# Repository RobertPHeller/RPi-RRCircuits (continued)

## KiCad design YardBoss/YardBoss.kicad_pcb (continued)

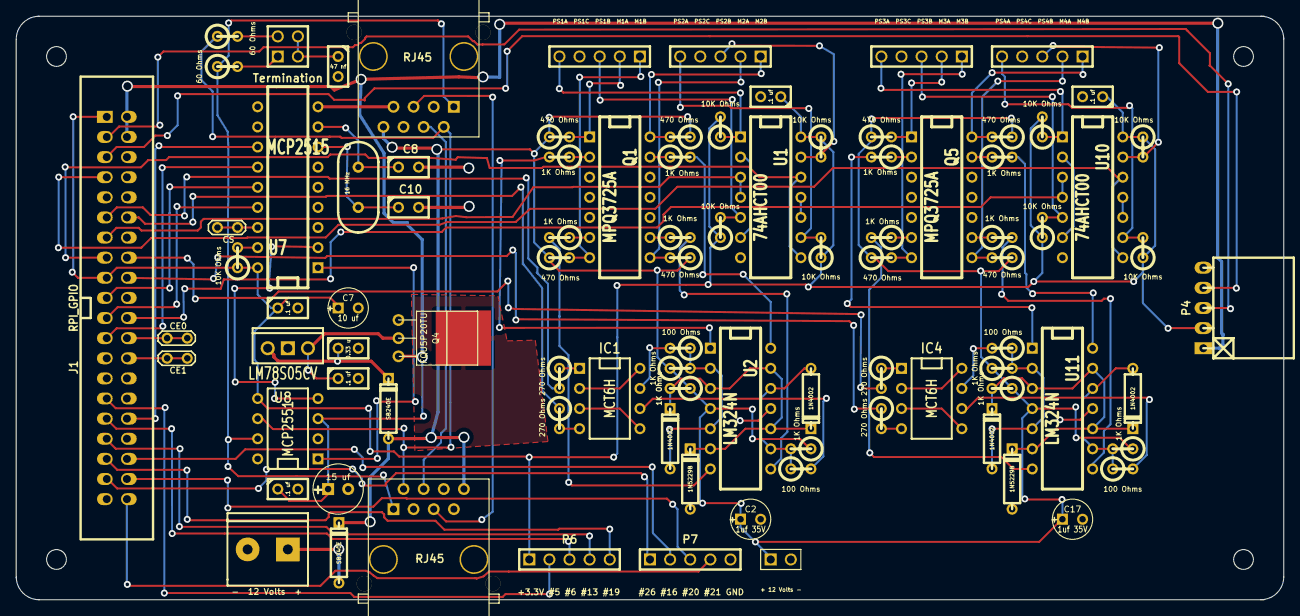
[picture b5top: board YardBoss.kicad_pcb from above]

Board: 2 copper layers, 160.0 x 73.7 mm, 95 parts (0 on the bottom side), 94 nets.

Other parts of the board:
MH: MountingHole_2-5mm_RevA_Date21Jun2010
MH#2, MH#3, MH#4: MountingHole_2-5mm_RevA_Date21Jun2010
